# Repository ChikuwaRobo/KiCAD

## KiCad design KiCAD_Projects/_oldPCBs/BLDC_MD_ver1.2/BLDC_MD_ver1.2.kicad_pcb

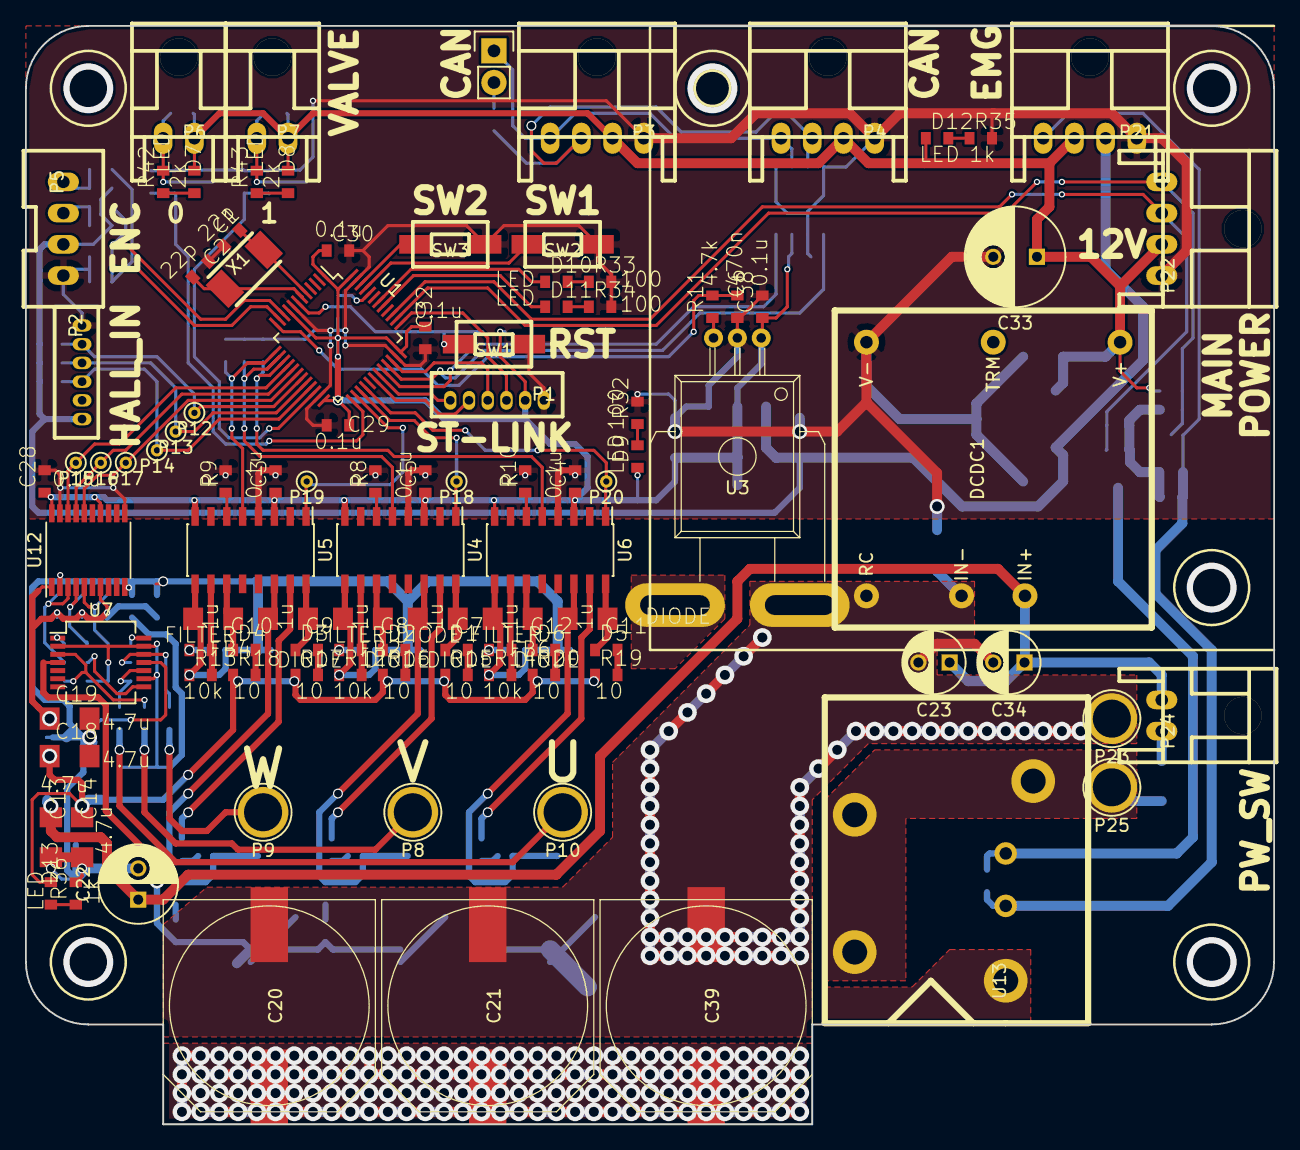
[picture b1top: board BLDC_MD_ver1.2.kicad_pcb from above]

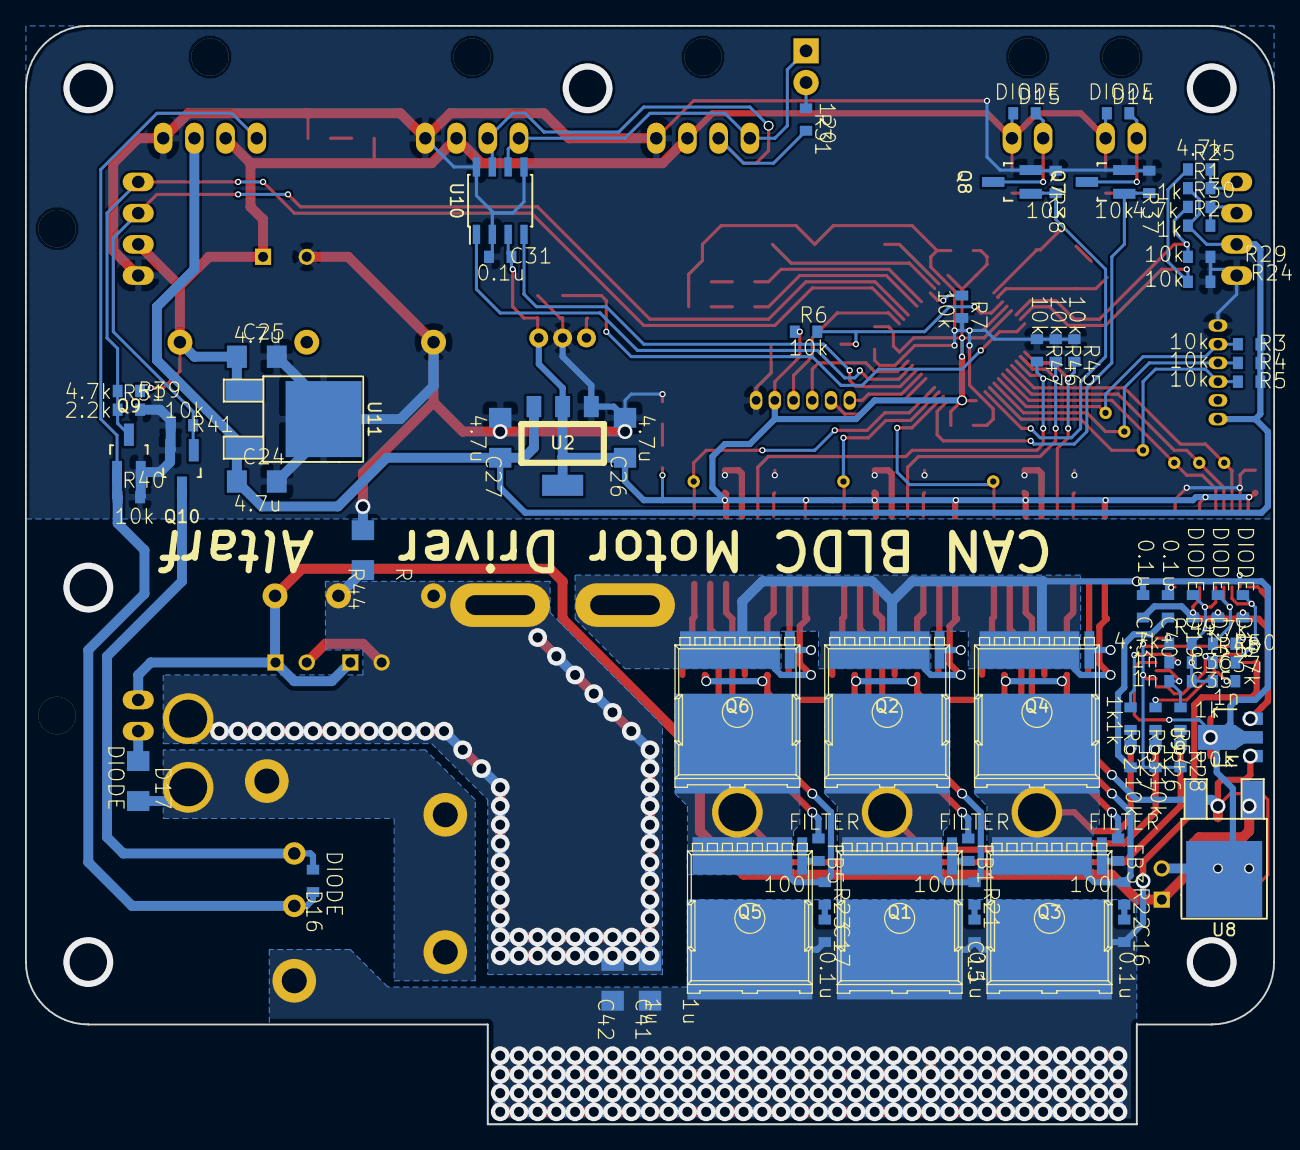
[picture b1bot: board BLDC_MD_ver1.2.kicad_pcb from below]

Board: 2 copper layers, 100.0 x 88.0 mm, 176 parts (74 on the bottom side), 105 nets.

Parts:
C1, C2: 22p; C1608_WP
C3, C4, C5, C15, C16, C17, C28, C29, C30, C31, C32, C38, C40, C43: 0.1u; C1608_WP
C6: 470n; C1608_WP
C7, C8, C9, C10, C11, C12, C41, C42: 1u; C3216
C13, C14, C18, C19, C24, C25, C26, C27: 4.7u; C3216
C20, C21, C39: 470u; c_elec_16x17
C22: 100u; C_Radial_D6.3_L11.2_P2.5
C23, C34: C; C_Radial_D5_L11_P2.5
C33: C; C_Radial_D8_L11.5_P3.5
C35, C36, C37: 1n; C1608_WP
D1, D2, D3, D4, D5, D6, D14, D15, D16, D18, D19, D20: DIODE; C1608_WP
D7, D8, D9, D10, D11, D12, D13: LED; C1608_WP
D17: DIODE; C3216
DCDC1: MGS15
FB1, FB2, FB3, FB4, FB5, FB6: FILTER; C1608_WP
P1, P2: CONN_01X06; ZH_6T
P3, P4, P21, P22: CONN_01X04; XA_4LC
P5: CONN_01X04; XA_4T
P6, P7, P24: CONN_01X02; XA_2LC
P8, P9, P10, P23, P25: CONN_01X01; 1pin
P11: CONN_01X02; Pin_Header_Straight_1x02
P12, P13, P14, P15, P16, P17, P18, P19, P20: CONN_01X01; PINTST
Q1, Q2, Q3, Q4, Q5, Q6: MOSFET_N; HSOF-8-1
Q7, Q8, Q9, Q10: MOSFET_N; SOT-23_Handsoldering
R1, R2, R35, R36, R52, R53, R54: 1k; C1608_WP
R3, R4, R5, R6, R7, R12, R13, R14, R24, R26, R27, R28, R29, R37, R38, R40, R41, R45, R46, R47: 10k; C1608_WP
R8, R9, R10: R; C1608_WP
R11, R25, R30, R39, R48, R49, R50: 4.7k; C1608_WP
R15, R16, R17, R18, R19, R20: 10; C1608_WP
R21, R22, R23, R32, R33, R34: 100; C1608_WP
R31: 120; C1608_WP
R42, R43: 2k; C1608_WP
R44: R; C3216
R51: 2.2k; C1608_WP
SW1, SW2, SW3: SW_PUSH; RP_SMD_Button
U1: STM32F103_48; LQFP-48_7x7mm_Pitch0.5mm
U2: NCP1117ST33T3G; SOT-223_reg
U3: ACS758; ACS785xCB
U4, U5, U6: SI8234; SOIC-16_3.9x9.9mm_Pitch1.27mm
U7: LM324; SSOP-14_5.3x6.2mm_Pitch0.65mm
U8: LM7812ACT; TO-252-2Lead
U9: LM7805CT; SOT89-3_Housing
U10: MAX3051; SOIC-8_3.9x4.9mm_Pitch1.27mm
U11: LM7805CT; TO-252-2Lead
U12: ADUM7640; TSSOP-20_4.4x6.5mm_Pitch0.65mm
U13: V23076-D3001-D142; V23076-A3001-D142
X1: CRYSTAL; ABM3_2pads

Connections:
+3.3V: C3.1, C4.1, C5.1, C26.1, C28.1, C29.1, C30.1, C31.1, C32.1, C38.1, D9.1, P1.2, R6.1, U1.1, U1.9, U1.24, U1.36, U1.48, U2.2, U3.1, U4.3, U4.8, U5.3, U5.8, U6.3, U6.8, U10.3, U12.14, U12.20
+5V: C24.1, C27.1, P2.6, P5.2, P21.2, R1.1, R2.1, R3.1, R4.1, R5.1, U2.3, U11.3
+12V: C25.1, C33.1, D7.1, D8.1, D12.1, D14.1, D15.1, DCDC1.1, P3.2, P4.2, P6.1, P7.1, P21.3, P22.2, R39.1, U11.1
+BATT: C15.1, C16.2, C17.2, C20.1, C21.1, C39.1, C41.1, C42.1, Q1.D, Q3.D, Q5.D, U7.4, U13.5
/BOOT0: R7.1, U1.44
/CAN_H: P3.3, P4.3, R31.2, U10.7
/CAN_L: P3.4, P4.4, P11.1, U10.6
/CAN_RX: U1.32, U10.4
/CAN_TX: U1.33, U10.1
/COMP_U: P15.1, U1.16, U12.18
/COMP_V: P16.1, U1.17, U12.17
/COMP_W: P17.1, U1.18, U12.16
/EMG: D16.1, P21.4, Q9.G, R40.1, U13.1
/EMG_OUT: P22.4, Q9.D, R39.2, R51.1, U1.38
/ENC_A: P5.3, R2.2, R30.2
/ENC_B: P5.4, R1.2, R25.2
/EN_U: R47.2, U1.15, U6.5
/EN_V: R46.2, U1.14, U4.5
/EN_W: R45.2, U1.13, U5.5
/GD_12V: C14.1, C18.1, D13.1, R15.1, R16.1, R17.1, R18.1, R19.1, R20.1, U8.3, U9.1
/HALL_0: P2.2, P12.1, R3.2, U1.19
/HALL_1: P2.3, P13.1, R4.2, U1.20
/HALL_2: P2.4, P14.1, R5.2, U1.21
/I_SENSE: C6.1, R11.2, U1.12
/LED_A: D10.1, U1.42
/LED_B: D11.1, U1.41
/NRST: R6.2, SW1.2, U1.7
/OUT_CENTER: C35.1, C36.1, C37.1, C40.1, R26.2, R27.2, R28.2, U7.2, U7.9, U7.13
/OUT_U: C11.2, P10.1, Q5.S, Q6.D, R23.1, R28.1, R54.1, U6.14
/OUT_V: C7.2, P8.1, Q1.S, Q2.D, R21.1, R26.1, R53.1, U4.14
/OUT_W: C9.2, P9.1, Q3.S, Q4.D, R22.1, R27.1, R52.1, U5.14
/POWER_EN: P22.3, Q10.G, R41.1, U1.39
/PWM_U: P20.1, U1.28, U6.1
/PWM_V: P18.1, U1.27, U4.1
/PWM_W: P19.1, U1.26, U5.1
/PW_5V: C19.1, C43.1, D18.1, D19.1, D20.1, U9.3, U12.1, U12.7
/PW_PW: C13.1, C22.1, C23.1, C34.1, DCDC1.6, P24.2, U8.1
/SW1: SW2.2, U1.45
/SW2: SW3.2, U1.46
/SWCLK: P1.3, U1.37
/SWDIO: P1.4, U1.34
/USART_RX: P1.6, U1.31
/USART_TX: P1.5, U1.30
/VALVE_0: Q7.G, R37.1, U1.25
/VALVE_1: Q8.G, R38.1, U1.22
GND: C1.1, C2.1, C3.2, C4.2, C5.2, C6.2, C24.2, C25.2, C26.2, C27.2, C28.2, C29.2, C30.2, C31.2, C32.2, C33.2, C38.2, DCDC1.3, P1.1, P2.1, P3.1, P4.1, P5.1, P21.1, P22.1, Q7.S, Q8.S, Q9.S, Q10.S, R7.2, R8.2, R9.2, R10.2, R24.1, R29.1, R32.2, R33.2, R34.2, R35.2, R37.2, R38.2, R40.2, R41.2, R44.2, R45.1, R46.1, R47.1, R51.2, SW1.1, SW2.1, SW3.1, U1.8, U1.23, U1.35, U1.47, U2.1, U3.2, U4.4, U5.4, U6.4, U10.2, U10.5, U10.8, U11.2, U12.11, U12.19
GNDPWR: C8.2, C10.2, C12.2, C13.2, C14.2, C18.2, C19.2, C22.2, C40.2, C43.2, Q2.S, Q4.S, Q6.S, R12.1, R13.1, R14.1, R36.2, U3.4, U4.9, U5.9, U6.9, U7.11, U8.2, U9.2, U12.2, U12.10
unnamed: C1.2, U1.5, X1.1
unnamed: C2.2, U1.6, X1.2
unnamed: C7.1, D1.1, U4.16
unnamed: C8.1, D2.1, U4.11
unnamed: C9.1, D3.1, U5.16
unnamed: C10.1, D4.1, U5.11
unnamed: C11.1, D5.1, U6.16
unnamed: C12.1, D6.1, U6.11
unnamed: C15.2, R21.2
unnamed: C16.1, R22.2
unnamed: C17.1, R23.2
unnamed: C20.2, C21.2, C23.2, C34.2, C39.2, C41.2, C42.2, DCDC1.4, DCDC1.5, P23.1, R44.1, U3.5
unnamed: C35.2, R54.2, U7.10
unnamed: C36.2, R52.2, U7.12
unnamed: C37.2, R53.2, U7.3
unnamed: D1.2, R15.2
unnamed: D2.2, R16.2
unnamed: D3.2, R17.2
unnamed: D4.2, R18.2
unnamed: D5.2, R19.2
unnamed: D6.2, R20.2
unnamed: D7.2, R42.1
unnamed: D8.2, R43.1
unnamed: D9.2, R32.1
unnamed: D10.2, R33.1
unnamed: D11.2, R34.1
unnamed: D12.2, R35.1
unnamed: D13.2, R36.1
unnamed: D14.2, P6.2, Q7.D, R42.2
unnamed: D15.2, P7.2, Q8.D, R43.2
unnamed: D16.2, Q10.D, U13.2
unnamed: D17.1, P24.1
unnamed: D17.2, P25.1, U13.4
unnamed: D18.2, R48.2, U12.3
unnamed: D19.2, R49.2, U12.5
unnamed: D20.2, R50.2, U12.4
unnamed: FB1.1, U4.15
unnamed: FB1.2, Q1.G
unnamed: FB2.1, R12.2, U4.10
unnamed: FB2.2, Q2.G
unnamed: FB3.1, U5.15
unnamed: FB3.2, Q3.G
unnamed: FB4.1, R13.2, U5.10
unnamed: FB4.2, Q4.G
unnamed: FB5.1, U6.15
unnamed: FB5.2, Q5.G
unnamed: FB6.1, R14.2, U6.10
unnamed: FB6.2, Q6.G
unnamed: P11.2, R31.1
unnamed: R8.1, U4.6
unnamed: R9.1, U5.6
unnamed: R10.1, U6.6
unnamed: R11.1, U3.3
unnamed: R24.2, R25.1, U1.11
unnamed: R29.2, R30.1, U1.10
unnamed: R48.1, U7.8
unnamed: R49.1, U7.14
unnamed: R50.1, U7.1

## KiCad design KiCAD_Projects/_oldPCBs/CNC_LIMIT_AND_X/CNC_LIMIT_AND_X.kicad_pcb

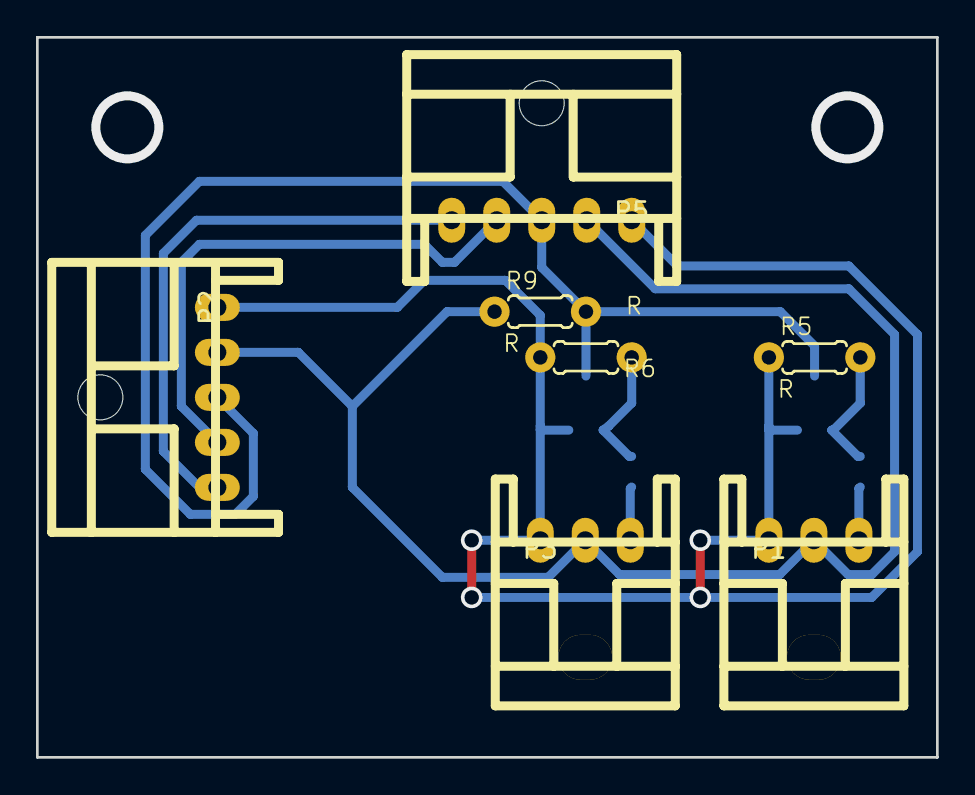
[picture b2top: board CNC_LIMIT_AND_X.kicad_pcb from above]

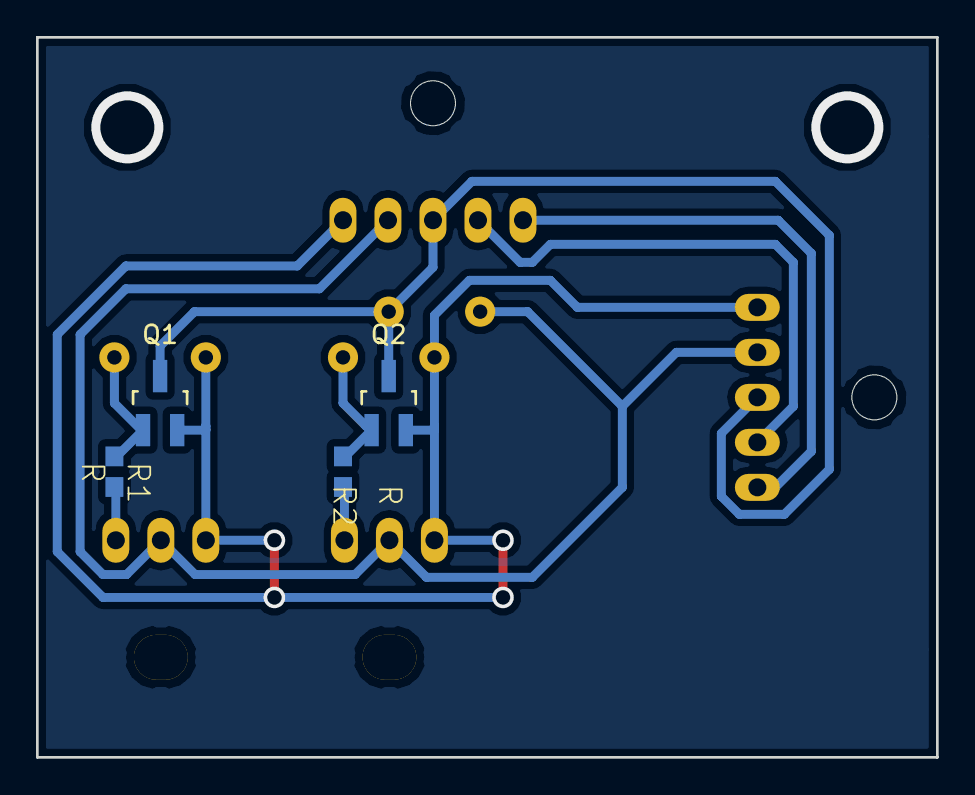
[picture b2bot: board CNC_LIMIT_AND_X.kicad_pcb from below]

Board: 2 copper layers, 50.0 x 40.0 mm, 11 parts (4 on the bottom side), 9 nets.

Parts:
P1, P3: CONN_01X03; XA_3L
P2, P5: CONN_01X05; XA_5L
Q1, Q2: MOSFET_N; SOT-23_Handsoldering
R1, R2: R; C1608
R5, R6, R9: R; 0204_2f5

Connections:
+5V: P1.2, P2.2, P3.2, P5.2, R9.1
/OUT_A: P2.3, P5.3, Q1.D, Q2.D, R9.2
GND: P1.1, P2.1, P3.1, P5.1, Q1.S, Q2.S, R5.1, R6.2
unnamed: P1.3, R1.2
unnamed: P2.4, P5.4
unnamed: P2.5, P5.5
unnamed: P3.3, R2.1
unnamed: Q1.G, R1.1, R5.2
unnamed: Q2.G, R2.2, R6.1

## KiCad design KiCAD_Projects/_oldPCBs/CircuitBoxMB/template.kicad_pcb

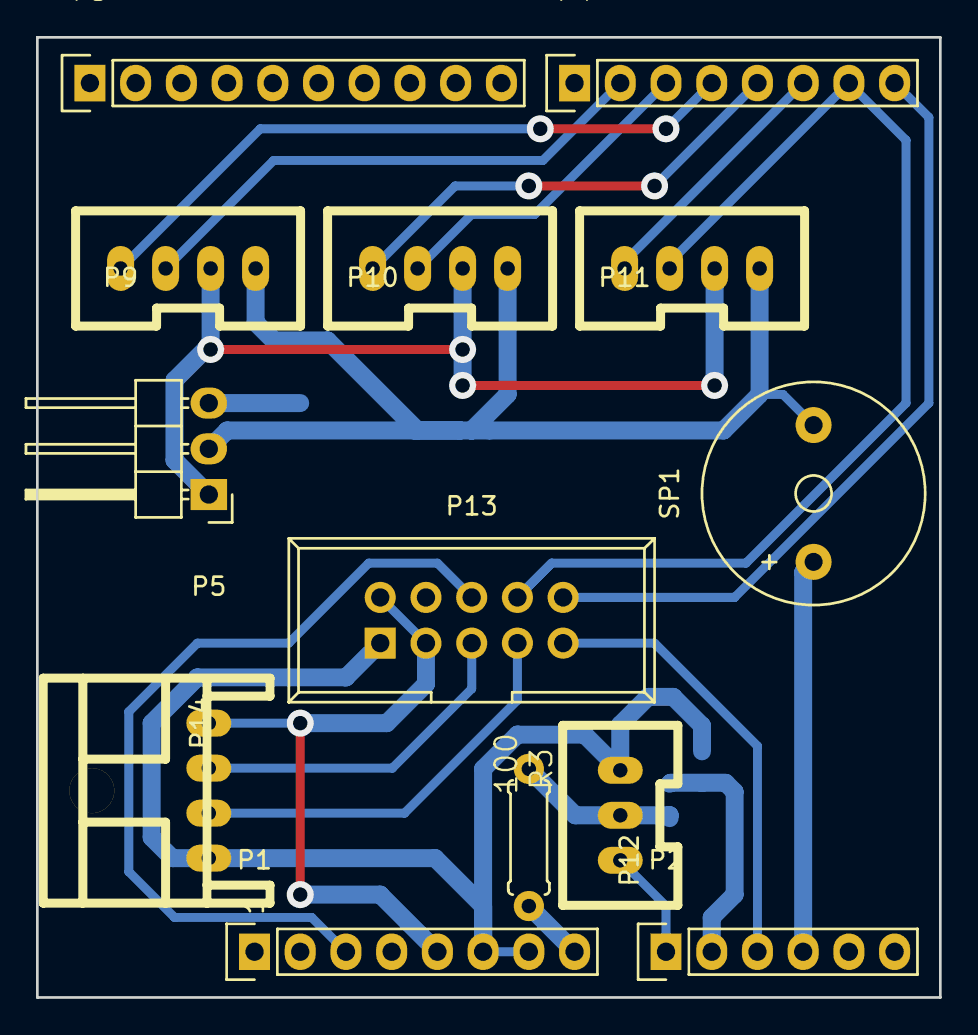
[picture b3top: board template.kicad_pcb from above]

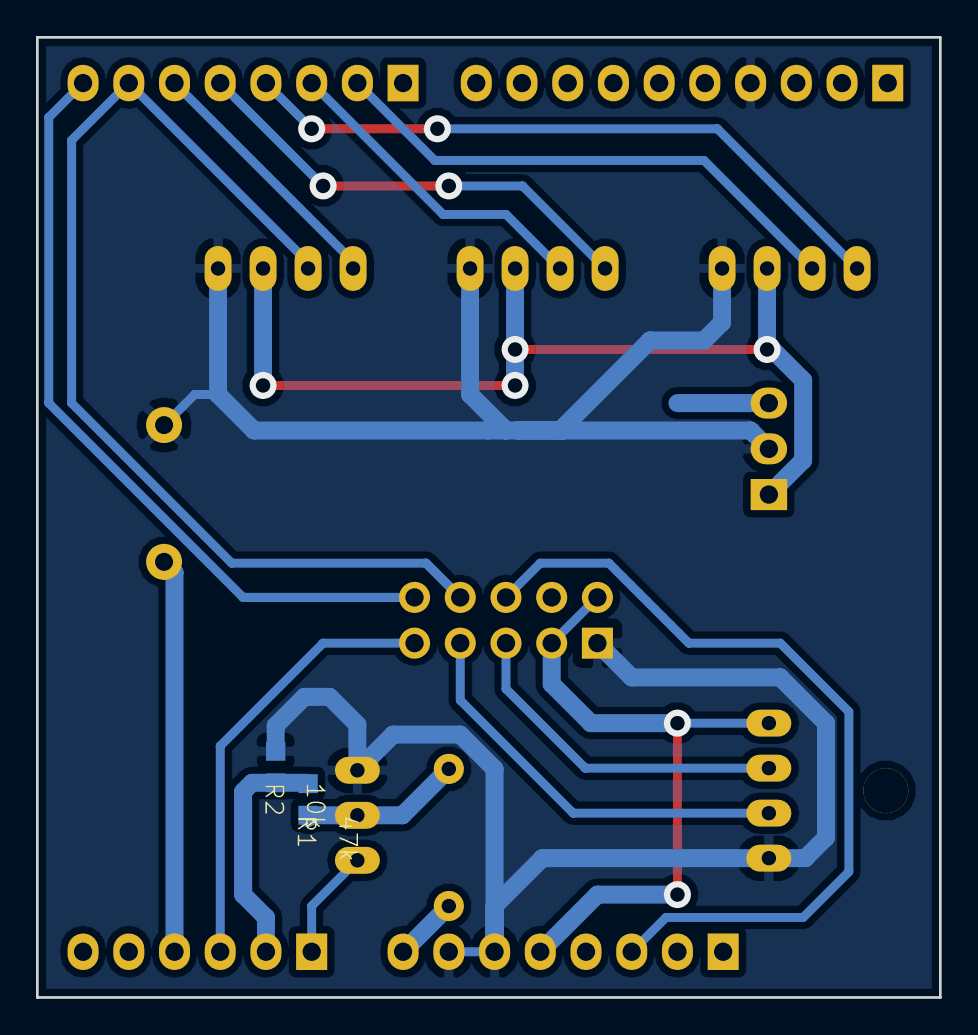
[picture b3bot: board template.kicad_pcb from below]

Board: 2 copper layers, 50.2 x 53.3 mm, 15 parts (2 on the bottom side), 21 nets.

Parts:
P1: Power; Socket_Strip_Straight_1x08
P2: Analog; Socket_Strip_Straight_1x06
P3: Digital; Socket_Strip_Straight_1x10
P4: Digital; Socket_Strip_Straight_1x08
P5: CONN_01X03; Pin_Header_Angled_1x03
P9, P10, P11: CONN_01X04; XA_4T
P12: CONN_01X03; XA_3T
P13: CONN_02X05; IDC_Header_Straight_10pins
P14: CONN_01X04; XA_4S
R1: 47k; C0603K
R2: 10k; C0603K
R3: 100; 0207_2f7
SP1: SPEAKER; Buzzer_12x9.5RM7.6

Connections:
5V_rerays: P5.1, P9.2, P10.2, P11.2
+5V: P1.5, P13.2, P13.3, P14.1
/0(Rx): P4.8, P13.10
/1(Tx): P4.7, P11.3, P13.8
/2: P4.6, P11.4
/3(**): P4.5, P10.4
/4: P4.4, P9.4
/5(**): P4.3, P10.3
/6(**): P4.2, P9.3
/A0: P2.1, P12.3
/A1: P2.2, R1.2, R2.1
/A2: P2.3, P13.9
/A3: P2.4, SP1.1
/A4(SDA): P2.5, P3.2
/A5(SCL): P2.6, P3.1
/Reset: P1.3, P13.6
/Vin: P1.8, P5.3, R3.2
GND: P1.6, P1.7, P3.4, P5.2, P9.1, P10.1, P11.1, P12.1, P13.1, P14.4, R2.2, SP1.2
unnamed: P12.2, R1.1, R3.1
USB_DM: P13.5, P14.2
USB_DP: P13.7, P14.3

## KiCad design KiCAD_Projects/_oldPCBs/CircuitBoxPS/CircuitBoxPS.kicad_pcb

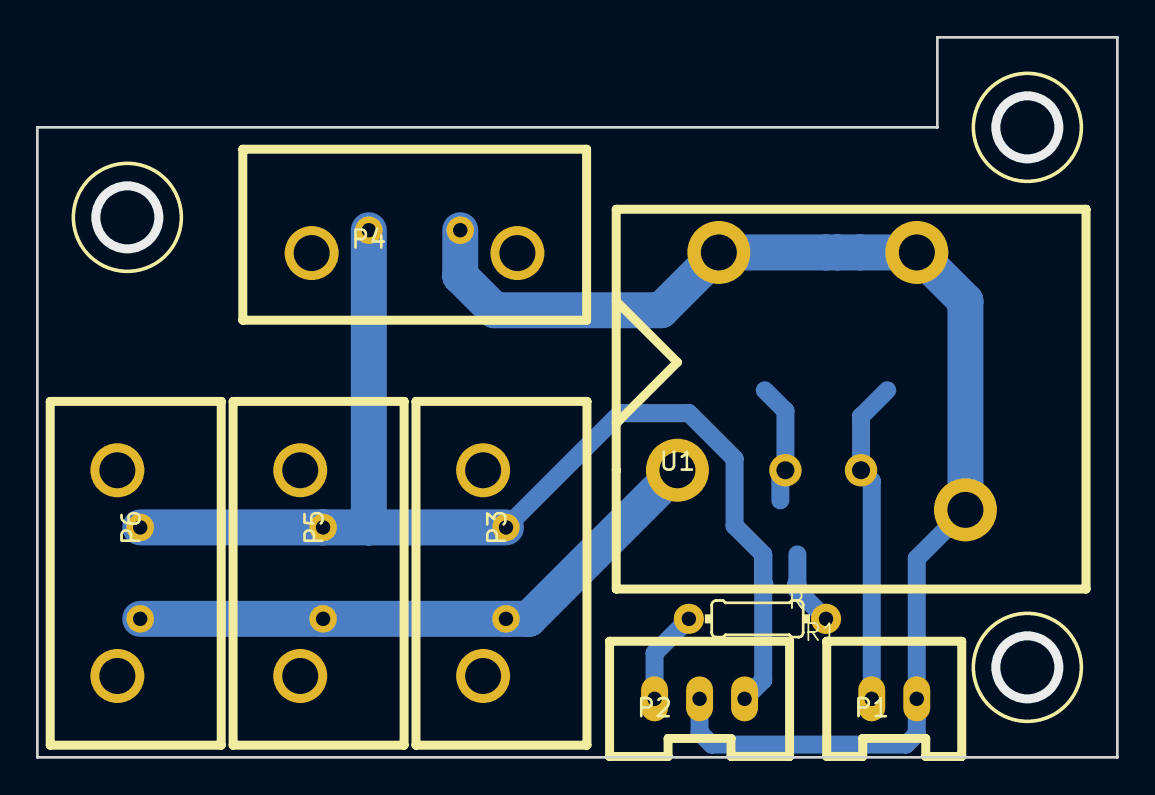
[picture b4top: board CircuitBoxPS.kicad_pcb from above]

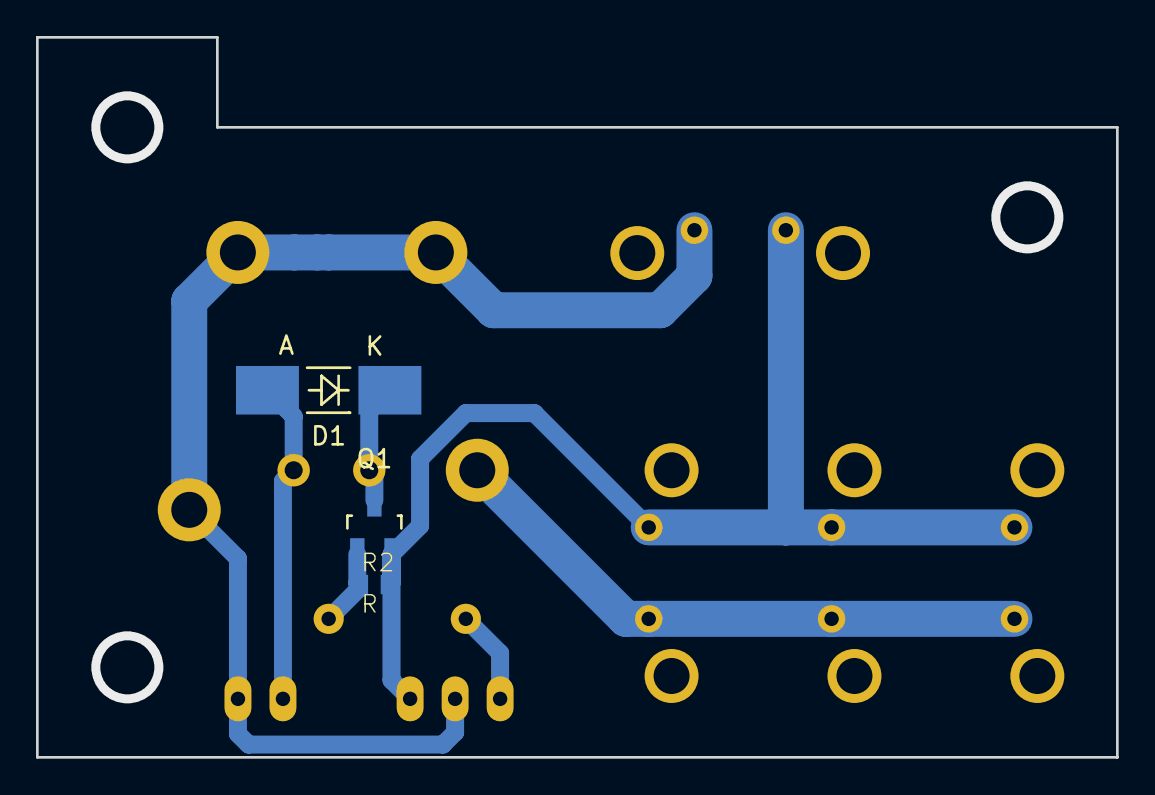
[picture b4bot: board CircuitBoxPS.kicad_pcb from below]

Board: 2 copper layers, 60.0 x 40.0 mm, 11 parts (3 on the bottom side), 7 nets.

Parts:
D1: DIODE; MELF_Handsoldering
P1: CONN_01X02; XA_2T
P2: CONN_01X03; XA_3T
P3, P4, P5, P6: CONN_01X02; D3200_2T
Q1: MOSFET_N; SOT-23_Handsoldering
R1: R; 0204_2f7
R2: R; C0603K
U1: V23076-D3001-D142; V23076-A3001-D142

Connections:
+BATT: P1.1, P2.2, P4.2, U1.4
/OUT: P3.2, P5.2, P6.2, U1.5
GNDPWR: P2.1, P3.1, P4.1, P5.1, P6.1, Q1.S, R2.2
unnamed: D1.1, Q1.D, U1.1
unnamed: D1.2, P1.2, U1.2
unnamed: P2.3, R1.2
unnamed: Q1.G, R1.1, R2.1

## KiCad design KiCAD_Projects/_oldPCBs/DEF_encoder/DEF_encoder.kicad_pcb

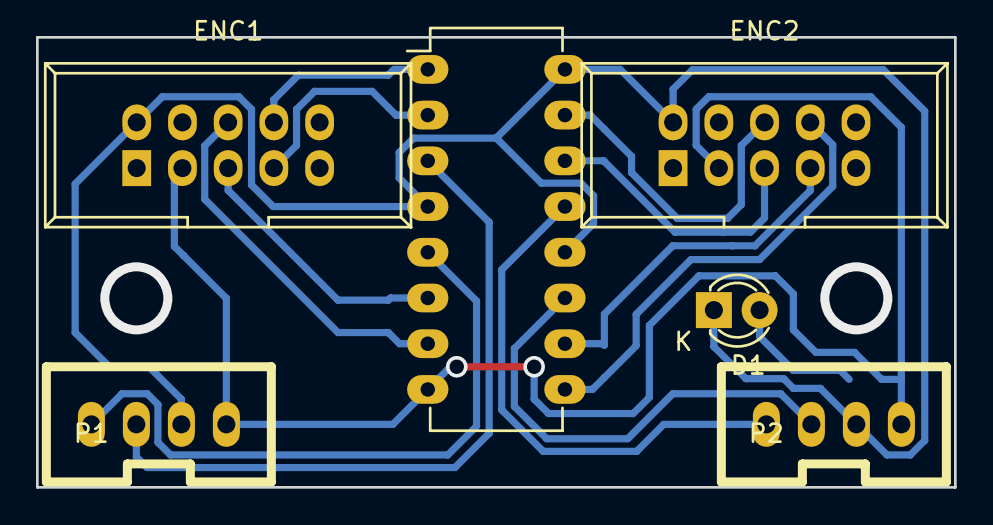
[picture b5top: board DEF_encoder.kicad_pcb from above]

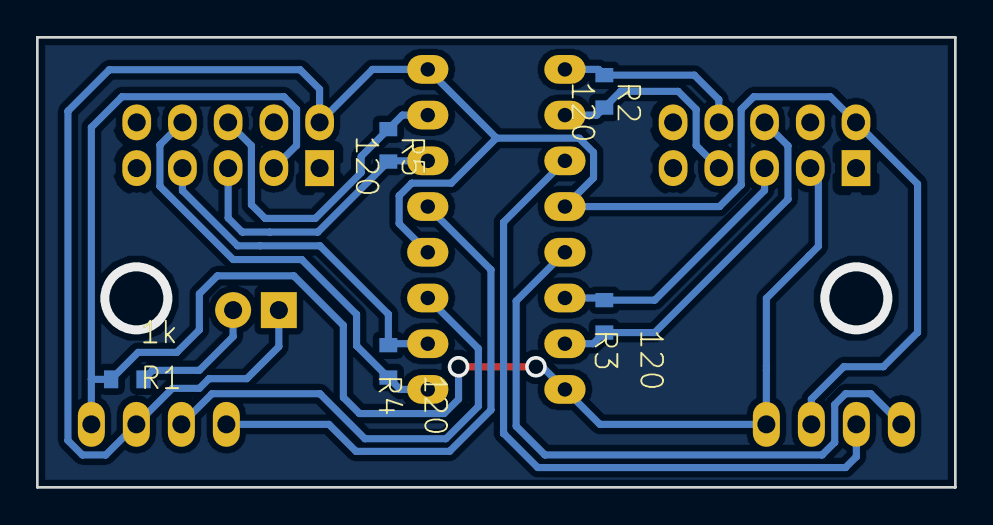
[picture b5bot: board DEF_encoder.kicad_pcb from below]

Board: 2 copper layers, 51.0 x 25.0 mm, 11 parts (5 on the bottom side), 15 nets.

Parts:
D1: LED; LED-3MM
ENC1, ENC2: RS422_ENCODER; DEF_ENCODER
P1, P2: CONN_01X04; XA_4T
R1: 1k; C1608_WP
R2, R3, R4, R5: 120; C1608_WP
U1: SN75175; DIP-16_W7.62mm_LongPads

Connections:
+5V: D1.1, ENC1.2, ENC2.2, P1.2, P2.2, U1.4, U1.12, U1.16
/IN1_AA: ENC1.7, R2.2, U1.2
/IN1_AB: ENC1.8, R2.1, U1.1
/IN1_BA: ENC1.5, R3.2, U1.6
/IN1_BB: ENC1.6, R3.1, U1.7
/IN2_AA: ENC2.7, R4.2, U1.10
/IN2_AB: ENC2.8, R4.1, U1.9
/IN2_BA: ENC2.5, R5.2, U1.14
/IN2_BB: ENC2.6, R5.1, U1.15
/OUT1_A: P1.3, U1.3
/OUT1_B: P1.4, U1.5
/OUT2_A: P2.3, U1.11
/OUT2_B: P2.4, U1.13
GND: ENC1.3, ENC2.3, P1.1, P2.1, R1.2, U1.8
unnamed: D1.2, R1.1

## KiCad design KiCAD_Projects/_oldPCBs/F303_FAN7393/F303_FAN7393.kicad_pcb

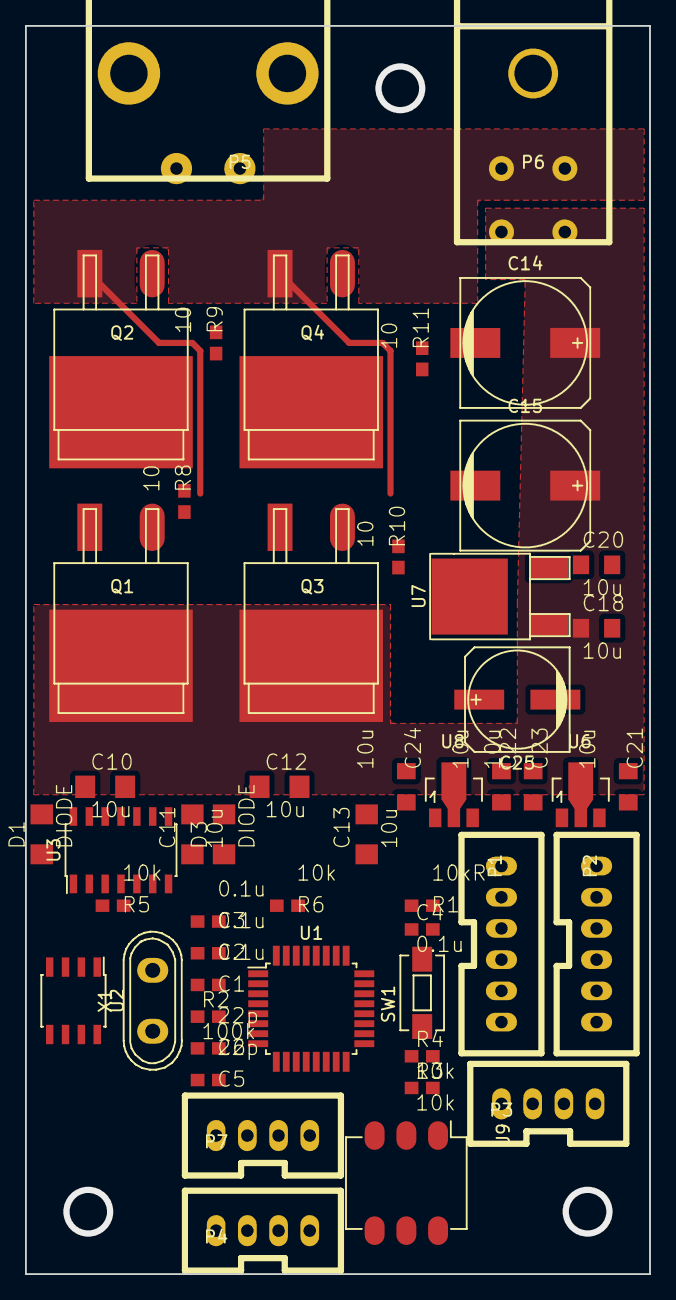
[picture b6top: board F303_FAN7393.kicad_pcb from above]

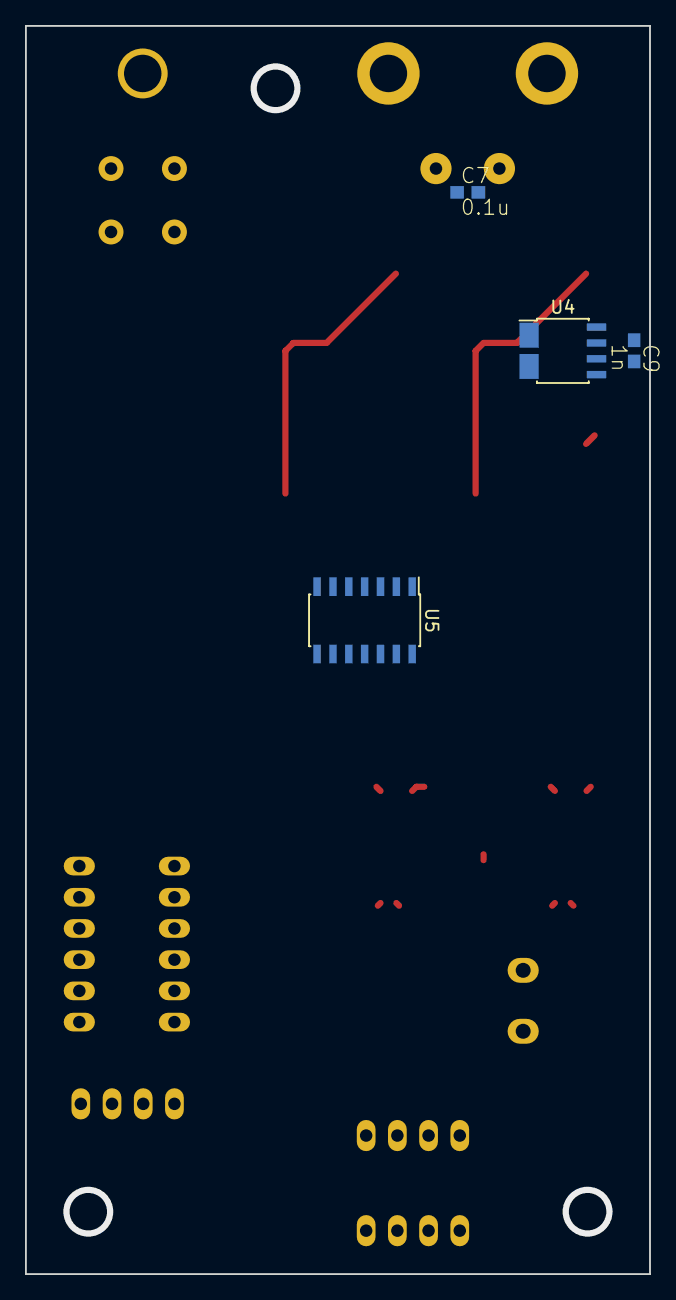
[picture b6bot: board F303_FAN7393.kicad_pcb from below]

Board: 2 copper layers, 50.0 x 100.0 mm, 55 parts (4 on the bottom side), 49 nets.

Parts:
C1, C2, C3, C4, C7: 0.1u; C1608
C5, C6: 22p; C1608
C9: 1n; C1608
C10, C11, C12, C13: 10u; C3216
C14, C15: 470u; c_elec_10x10.5
C18, C20, C21, C22, C23, C24: 10u; C2012
C25: 220u; c_elec_8x6.5
D1, D3: DIODE; C3216
P1, P2: CONN_01X06; XA_6T
P3, P4, P7: CONN_01X04; XA_4T
P5: CONN_01X02; D-3200S_2L
P6: CONN_01X04; D-3500D_4S
Q1, Q2, Q3, Q4: MOSFET_N; D2-PAK_GateEllipce
R1: 10kR; C1608
R2: 100k; C1608
R3, R4, R5, R6: 10k; C1608
R8, R9, R10, R11: 10; C1608
SW1: SW_PUSH; SW_SPST_EVQPE1
U1: STM32F303K8; TQFP-32_7x7mm_Pitch0.8mm
U2: MCP2551; SOIC-8_3.9x4.9mm_Pitch1.27mm
U3, U5: FAN7393; SOIC-14_3.9x8.7mm_Pitch1.27mm
U4: ACS714; SOIC-8_3.9x4.9mm_Pitch1.27mm_ACS
U6: NCP1117ST50T3G; SOT89-3_Housing
U7: MC78L15ACP; TO-252-2Lead
U8: NCP1117ST33T3G; SOT89-3_Housing
U9: SW_ROTARY_16
X1: CRYSTAL; Crystal_HC50-U_Vertical

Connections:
+3.3V: C1.1, C2.1, C3.1, C24.1, P1.2, R1.2, R3.1, R4.1, U1.1, U1.5, U1.17, U8.2
+5V: C22.1, C23.1, P3.2, U2.3, U4.8, U6.2, U8.3
+12V: P2.2, P4.2, P7.2
+BATT: C14.1, C15.1, C18.1, P6.2, P6.4, Q1.D, Q3.D, U7.1
/CAN_H: P4.4, P7.4, U2.7
/CAN_L: P4.3, P7.3, U2.6
/CAN_RX: U1.21, U2.4
/CAN_TX: U1.22, U2.1
/CURRENT_SENSE: U1.6, U4.7
/ENC_A: P3.3, P3.4, R3.2, R4.2, U1.27
/GD_PS: C11.1, C13.1, D1.1, D3.1, U3.7, U5.7
/GP_PS: C20.1, C21.1, C25.1, U6.3, U7.3
/OUT_A: C7.2, P5.2, U4.1, U4.2
/OUT_A_CS: C10.2, Q1.S, Q2.D, U3.11, U4.3, U4.4
/OUT_B: C7.1, C12.2, P5.1, Q3.S, Q4.D, U5.11
/PWM_A: U1.25, U3.1
/PWM_B: U1.26, U5.1
/ROTARY_1: U1.15, U9.1
/ROTARY_2: U1.18, U9.3
/ROTARY_4: U1.19, U9.4
/ROTARY_8: U1.20, U9.6
/SPI1_MISO/POT: P2.4, U1.12
/SPI1_MOSI: P2.3, U1.13
/SPI1_NSS/LIMIT_A: P2.6, U1.10
/SPI1_SCK/LIMIT_B: P2.5, U1.11
/USART1_RX: P1.6, U1.30
/USART1_TX: P1.5, U1.29
/~SD: U3.2, U5.2
GND: C1.2, C2.2, C3.2, C4.1, C5.2, C6.2, C9.2, C21.2, C22.2, C23.2, C24.2, P1.1, P2.1, P3.1, P4.1, P7.1, R2.1, R5.2, R6.2, SW1.1, U1.16, U1.31, U1.32, U2.2, U3.3, U4.5, U5.3, U6.1, U8.1, U9.2, U9.5
GNDPWR: C11.2, C13.2, C14.2, C15.2, C18.2, C20.2, C25.2, P6.1, P6.3, Q2.S, Q4.S, U3.5, U5.5, U7.2
unnamed: C4.2, R1.1, SW1.2, U1.4
unnamed: C5.1, U1.3, X1.1
unnamed: C6.1, U1.2, X1.2
unnamed: C9.1, U4.6
unnamed: C10.1, D1.2, U3.13
unnamed: C12.1, D3.2, U5.13
unnamed: P1.3, U1.24
unnamed: P1.4, U1.23
unnamed: Q1.G, R8.1
unnamed: Q2.G, R9.1
unnamed: Q3.G, R10.1
unnamed: Q4.G, R11.1
unnamed: R2.2, U2.8
unnamed: R5.1, U3.4
unnamed: R6.1, U5.4
unnamed: R8.2, U3.12
unnamed: R9.2, U3.6
unnamed: R10.2, U5.12
unnamed: R11.2, U5.6

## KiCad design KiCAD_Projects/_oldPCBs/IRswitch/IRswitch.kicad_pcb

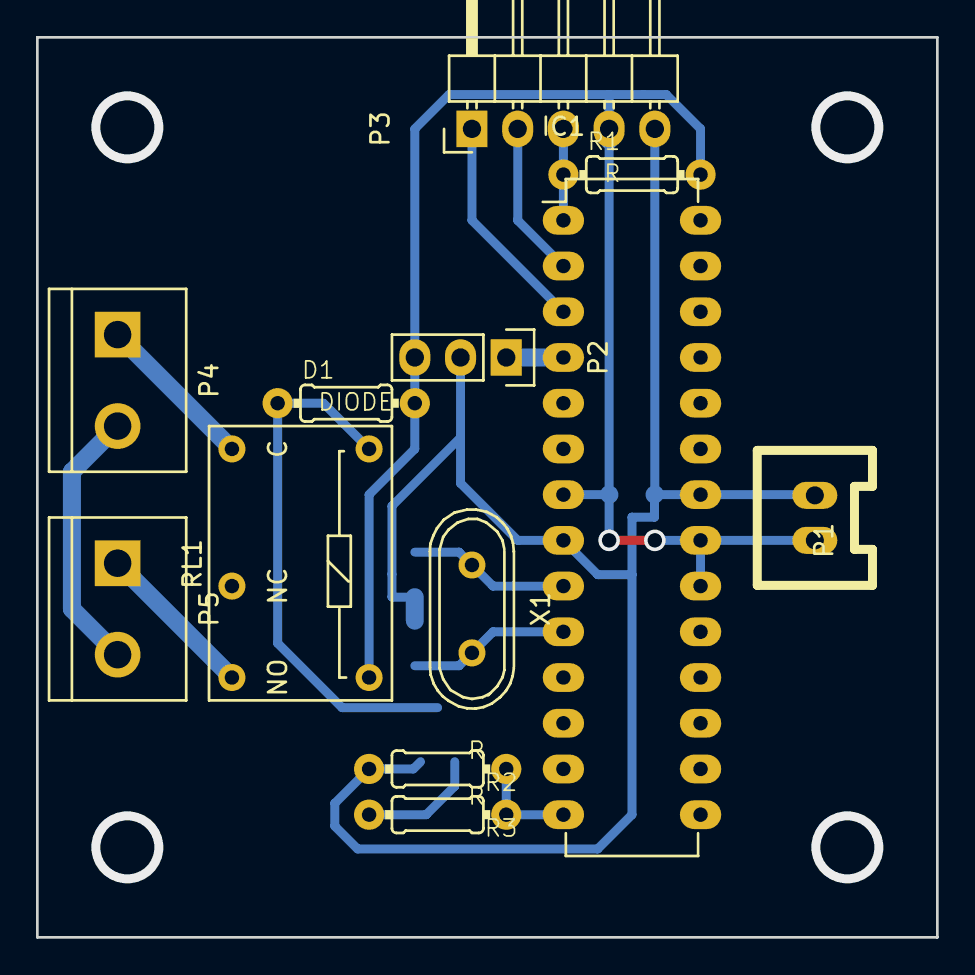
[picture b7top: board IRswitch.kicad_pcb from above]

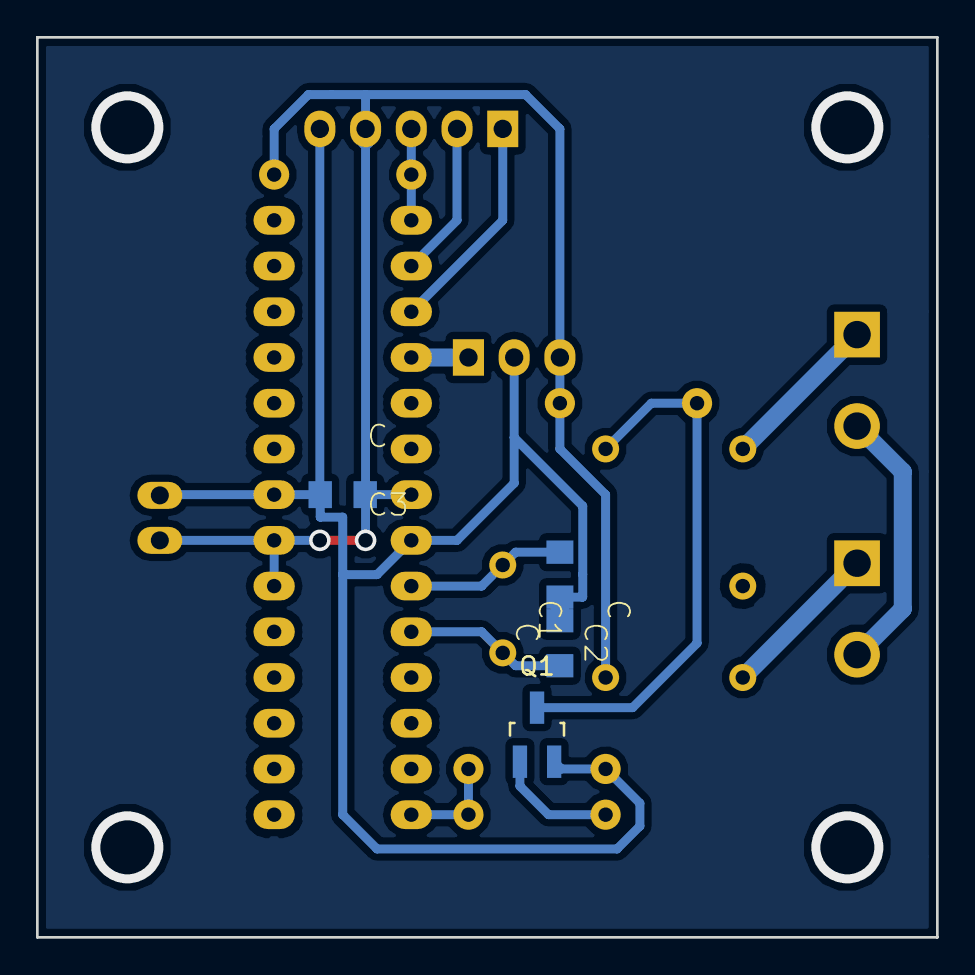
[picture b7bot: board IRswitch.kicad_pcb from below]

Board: 2 copper layers, 50.0 x 50.0 mm, 16 parts (4 on the bottom side), 14 nets.

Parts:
C1, C2, C3: C; C2012
D1: DIODE; 0204_2f7
IC1: ATMEGA168-P; DIP-28_W7.62mm_LongPads
P1: CONN_01X02; XA_2T
P2: CONN_01X03; Pin_Header_Straight_1x03
P3: CONN_01X05; Pin_Header_Angled_1x05
P4, P5: CONN_01X02; bornier2
Q1: MOSFET_N; SOT-23_Handsoldering
R1, R2, R3: R; 0204_2f7
RL1: OMRON_G6E; Relay_SPDS_OMRON-G6E
X1: CRYSTAL; Crystal_HC49-U_Vertical

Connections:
+5V: C3.1, D1.2, IC1.7, IC1.20, IC1.21, P1.2, P2.3, P3.4, R1.2, RL1.1
/IR: IC1.4, P2.1
/RELAY: IC1.14, R2.1, R3.1
/RX: IC1.2, P3.2
/TX: IC1.3, P3.1
/XTAL_1: C1.2, IC1.9, X1.1
/XTAL_2: C2.2, IC1.10, X1.2
/~RST: IC1.1, P3.3, R1.1
GND: C1.1, C2.1, C3.2, IC1.8, IC1.22, P1.1, P2.2, P3.5, Q1.S, R2.2
unnamed: D1.1, Q1.D, RL1.6
unnamed: P4.1, RL1.7
unnamed: P4.2, P5.2
unnamed: P5.1, RL1.12
unnamed: Q1.G, R3.2
